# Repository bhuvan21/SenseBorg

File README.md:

# SenseBorg
A modular platform for human sensory substitution via haptic feedback.

## Introduction
The concept of sensory substitution involves supplying sensory stimuli through a sensory modality usually used for gathering different sensory data  – and has an important role to play in rehabilitation those with vestibular impairments. Sensory substitution requires the use of a specific device, which uses artificial sensors to collect sensory data, and delivers this data to a subject via one of their sensory modalities (e.g touch, audio, visual). Devices which do this are called sensory substitution devices (SSDs).

## The Project
Sensory Substitution Devices require two parts.  
1. Some way to provide artificial stimuli  
2. Some way to generate this stimuli (usually a sensor of some kind)  

Good examples of this are the BrainPort and feelSpace belt devices. My project nicknamed "SenseBorg" (think Senses + Cyborg) is my contribution to this under-explored area of research.  

These two parts of my project are:
1. A custom belt, with up to 16 embedded haptic motors, for generating artificial stimuli with selectable position and strength.  
2. An IMU headband for sensing rotational acceleration, as an approximation of the sense of balance.  

The second part of the project can be easily substituted for any other sensor, which could be used to conduct experiments into learning other sensorimotor contingencies.  
Thus, this project provides a platform for providing artificial stimuli for use in more general sensory substitution experiments.

## The Belt
The specifics of the physical hardware in the SenseBorg belt is more detailed in the build folder, specifically BUILD.md. However, the basic features are as follows.  
- 12h battery life
- 16 different motor channels, each with PWM control
- Wifi enabled
- Bluetooth capabilities
- Modular as haptic motors can be placed variably on the belt to accomodate for different waist sizes
- ~2A Charging rate (if your charger can handle it) for overnight charging

## This Repository
This repository contains the software and hardware information for the SenseBorg belt itself. Of course, a lot of the software is specific to interfacing with my specific sensor system, and translating this into targeted haptic feedback. Please have a look at build/BUILD.md for a build guide. This project is currently in it's first iteration, so is subject to change and improvement.

## Results
After a first experiment, the hypothesis that the wearing of this belt would result in an increase in the wearer's sense of balance, was shown to be statistically significant. (Balance was tested via a sharpened Romberg Test, the belt was worn over a week period for 12 hours a day, the statistical difference was measured via a T-test, and the final p < 0.01)
My research paper based on this device is undergoing a final review at the Young Scientists Journal.

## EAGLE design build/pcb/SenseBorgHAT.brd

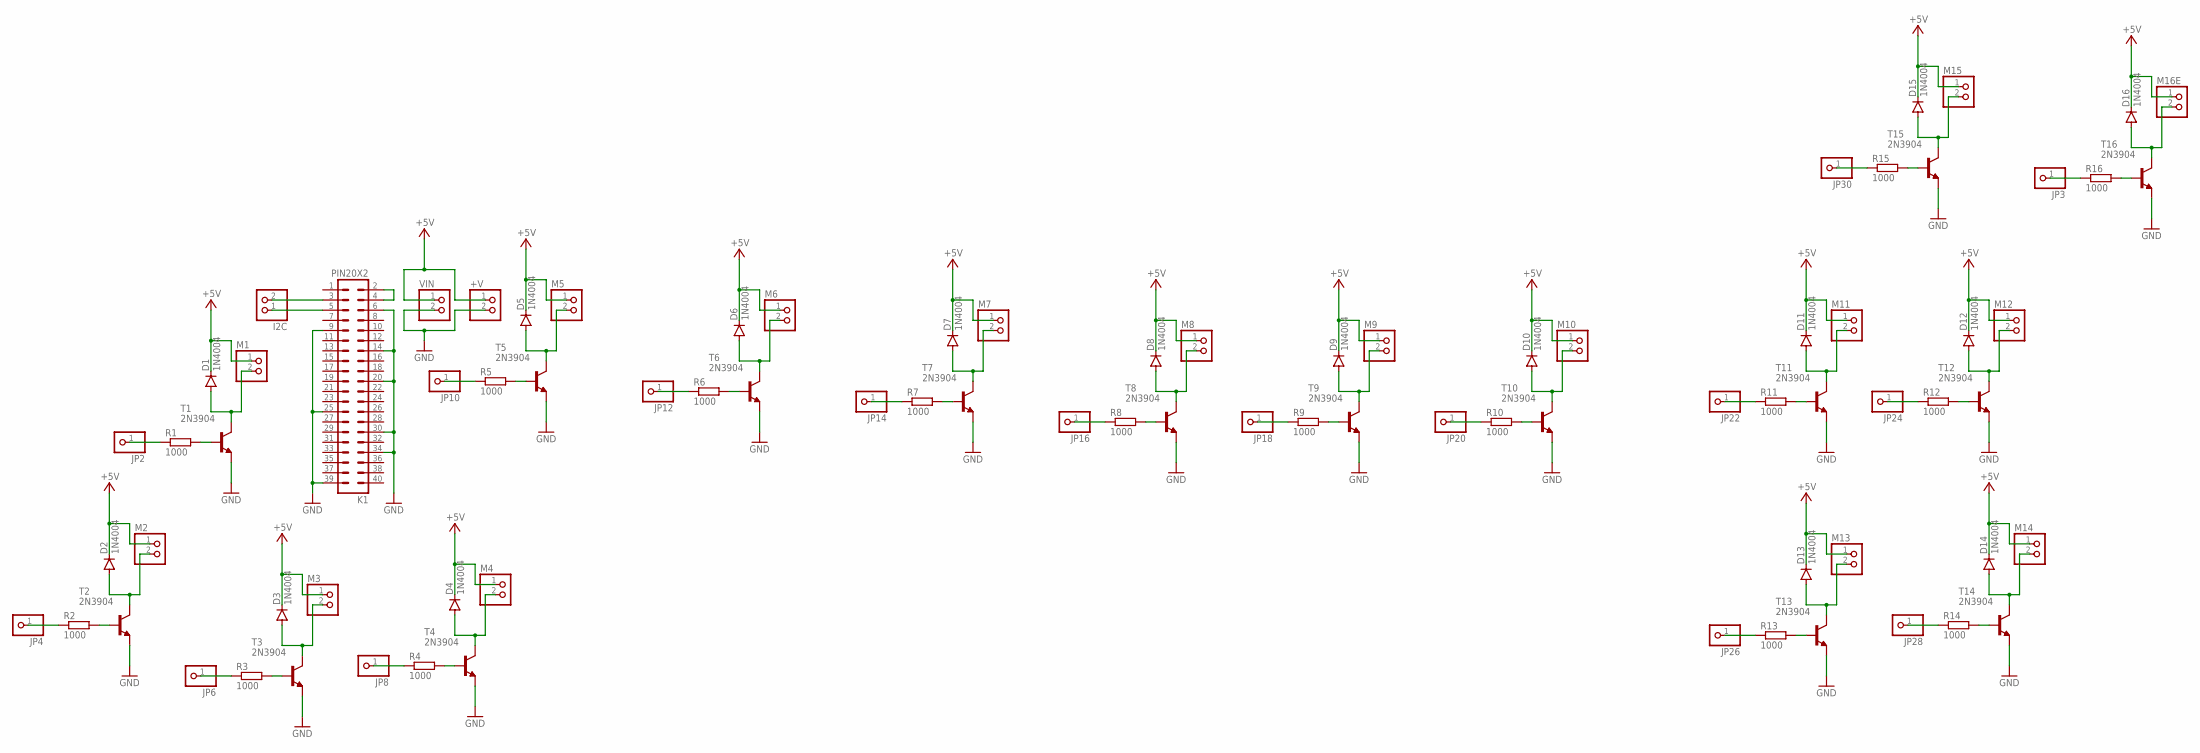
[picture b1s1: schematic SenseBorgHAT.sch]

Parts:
+V: PINHD-1X2; 1X02
D1, D2, D3, D4, D5, D6, D7, D8, D9, D10, D11, D12, D13, D14, D15, D16: 1N4004; DO41-10
I2C: PINHD-1X2; 1X02
JP2, JP3, JP4, JP6, JP8, JP10, JP12, JP14, JP16, JP18, JP20, JP22, JP24, JP26, JP28, JP30: PINHD-1X1; 1X01
K1: PIN20X2; PIN_20X2
M1, M2, M3, M4, M5, M6, M7, M8, M9, M10, M11, M12, M13, M14, M15, M16E: PINHD-1X2; 1X02
R1, R2, R3, R4, R5, R6, R7, R8, R9, R10, R11, R12, R13, R14, R15, R16: 1000; 0207/10
T1, T2, T3, T4, T5, T6, T7, T8, T9, T10, T11, T12, T13, T14, T15, T16: 2N3904; TO92
VIN: PINHD-1X2; 1X02

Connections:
+5V: +V.1, D1.C, D2.C, D3.C, D4.C, D5.C, D6.C, D7.C, D8.C, D9.C, D10.C, D11.C, D12.C, D13.C, D14.C, D15.C, D16.C, M1.1, M2.1, M3.1, M4.1, M5.1, M6.1, M7.1, M8.1, M9.1, M10.1, M11.1, M12.1, M13.1, M14.1, M15.1, M16E.1, VIN.1
+5V1: I2C.1, K1.5
GND: +V.2, K1.6, K1.9, K1.14, K1.20, K1.25, K1.30, K1.34, K1.39, T1.3 (E), T2.3 (E), T3.3 (E), T4.3 (E), T5.3 (E), T6.3 (E), T7.3 (E), T8.3 (E), T9.3 (E), T10.3 (E), T11.3 (E), T12.3 (E), T13.3 (E), T14.3 (E), T15.3 (E), T16.3 (E), VIN.2
M15: D10.A, M10.2, T10.1 (C)
unnamed: R1.2, T1.2 (B)
unnamed: D1.A, M1.2, T1.1 (C)
unnamed: JP2.1, R1.1
unnamed: R2.2, T2.2 (B)
unnamed: D2.A, M2.2, T2.1 (C)
unnamed: JP4.1, R2.1
unnamed: R3.2, T3.2 (B)
unnamed: D3.A, M3.2, T3.1 (C)
unnamed: JP6.1, R3.1
unnamed: R4.2, T4.2 (B)
unnamed: D4.A, M4.2, T4.1 (C)
unnamed: JP8.1, R4.1
unnamed: R5.2, T5.2 (B)
unnamed: D5.A, M5.2, T5.1 (C)
unnamed: JP10.1, R5.1
unnamed: R6.2, T6.2 (B)
unnamed: D6.A, M6.2, T6.1 (C)
unnamed: JP12.1, R6.1
unnamed: R7.2, T7.2 (B)
unnamed: D7.A, M7.2, T7.1 (C)
unnamed: JP14.1, R7.1
unnamed: R8.2, T8.2 (B)
unnamed: D8.A, M8.2, T8.1 (C)
unnamed: JP16.1, R8.1
unnamed: R9.2, T9.2 (B)
unnamed: D9.A, M9.2, T9.1 (C)
unnamed: JP18.1, R9.1
unnamed: R10.2, T10.2 (B)
unnamed: R16.2, T16.2 (B)
unnamed: JP20.1, R10.1
unnamed: R11.2, T11.2 (B)
unnamed: D11.A, M11.2, T11.1 (C)
unnamed: JP22.1, R11.1
unnamed: R12.2, T12.2 (B)
unnamed: D12.A, M12.2, T12.1 (C)
unnamed: JP24.1, R12.1
unnamed: R13.2, T13.2 (B)
unnamed: D13.A, M13.2, T13.1 (C)
unnamed: JP26.1, R13.1
unnamed: R14.2, T14.2 (B)
unnamed: D14.A, M14.2, T14.1 (C)
unnamed: JP28.1, R14.1
unnamed: R15.2, T15.2 (B)
unnamed: D15.A, M15.2, T15.1 (C)
unnamed: JP30.1, R15.1
unnamed: D16.A, M16E.2, T16.1 (C)
unnamed: JP3.1, R16.1
unnamed: I2C.2, K1.3
unnamed: K1.2, K1.4

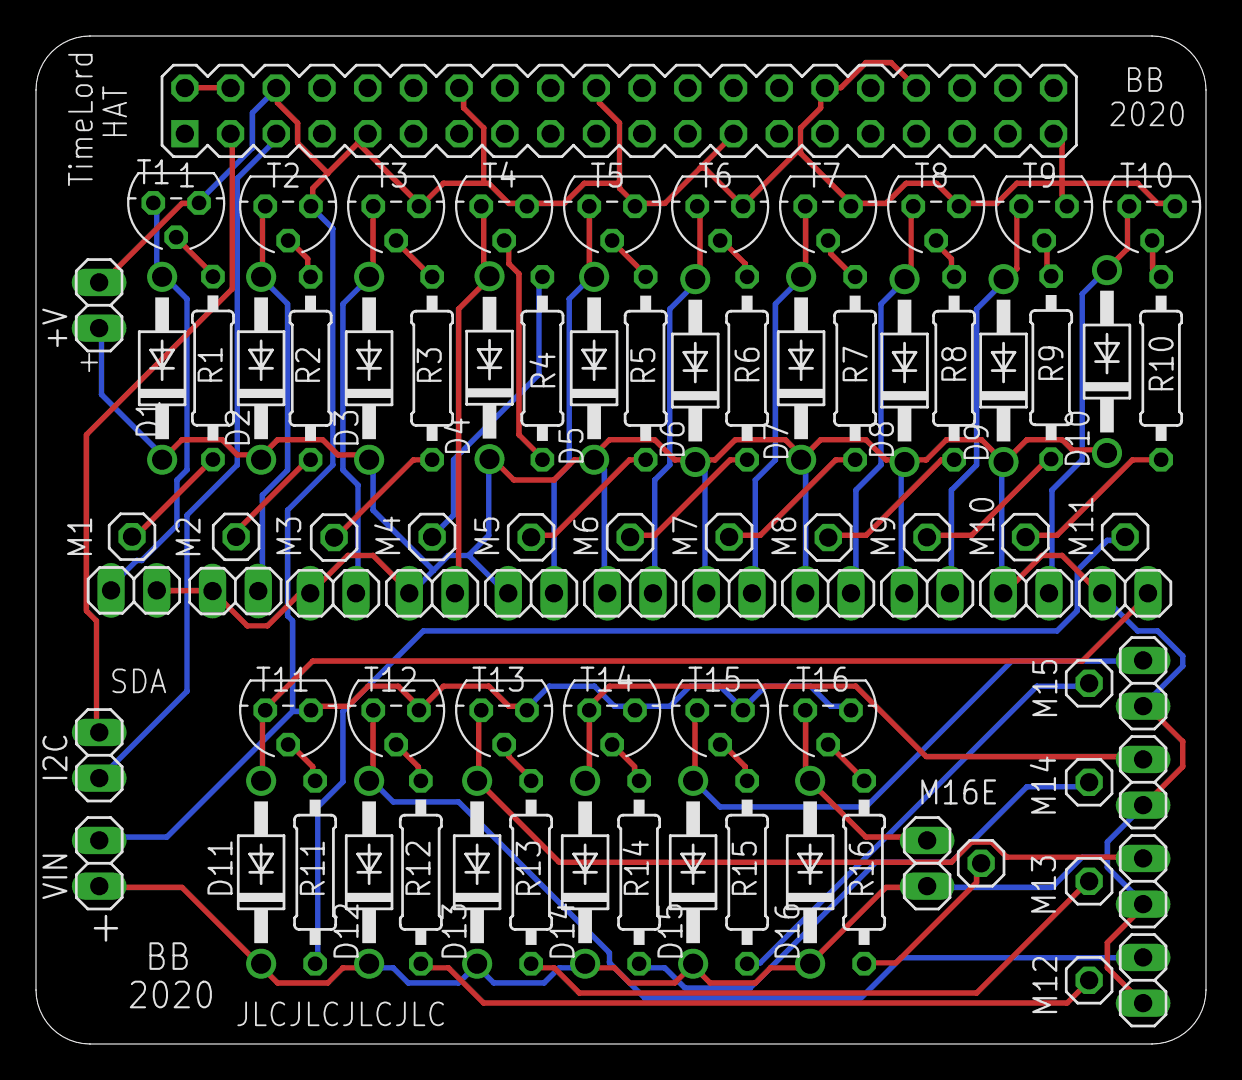
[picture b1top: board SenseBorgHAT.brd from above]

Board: 2 copper layers, 65.0 x 56.0 mm, 84 parts (0 on the bottom side), 53 nets.

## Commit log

2020-04-17 Sensor investigating
2020-04-21 lots of clean up + heading fusion done
2020-04-21 small bug fix
2020-04-21 Messy madgwick works - needs to be cleaned up
2020-04-21 cleanup
2020-04-21 final working clean
2020-04-21 Simple graphing help tool
2020-05-12 Pi import fixes
2020-05-12 i2c passthrough
2020-05-12 i2c passthrough2
2020-05-12 Server beginnings
2020-05-14 added network client side things
2020-05-14 v1 fixes
2020-05-15 Sensor getting fixes + better networking
2020-05-15 no db on git
2020-05-15 db works
2020-06-09 server updates
2020-06-09 build started
2020-06-09 build started 2
2020-06-10 added rev 1 of build guide, missing pics + diagrams
2020-06-10 testing image embed
2020-06-10 Added basic photos to BUILD
2020-06-10 JPG --> jpg
2020-06-10 cropped photos
2020-06-10 cropped photos2
2020-06-10 compacted assembly pics
2020-06-10 pcb things, circuit diagram, etc
2020-06-10 more pics
2020-06-10 small fixes
2020-06-10 photo resizing
2020-06-10 new photo
2020-06-10 stls
2020-06-11 added print guide
